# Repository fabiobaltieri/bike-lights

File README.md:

# Bike helmet head and tail light with remote control

This project is a head light and tail light electronic and CAD design,
featuring a handlebar mounted remote control for on/off operation, high beam
and rear stop light.

Contents
----------------

  - `cad`: FreeCAD source files for the various mechanical parts
  - `firmware-remote`: firmware for the remote control
  - `headlight`: hardware files for the head light LED carrier (Eagle)
  - `red-cluster`: hardware files for the rear light LED carrier (Eagle)
  - `remote`: hardware files for the remote controller (Eagle)

  TODO: add tail light pcb and firmware files.

Tail Light
----------

The tail light module contains the electronics and rechargeable battery.

Features:

  - Power drivers for front beam and rear lights (multiple channels).
  - Integrates a lithium battery charger via micro-USB (`MCP73831`).
  - Battery current and voltage monitoring (`INA219`).
  - Main microcontroller (`ATmega88PA`)
  - Low power radio for remote controlled operation (`nRF24L01+`).
  - Rear light uses an array of 4x3 red LEDs.

The module has a custom 3D printed case, and integrates a magnet to mount on
the rear helmet light slot found on many Giant helmets (meant to be used with
`Numen Link` lights). The magnet is glued to the case with epoxy.

Since the rear light module is removable, it includes two spring loaded
contacts (P/N: `Harwin P70-1020045R`) to drive the front headlight, which is
fixed on the helmet and wired to two matching copper tape pads on the rear
light slot.

  NOTE: the tail light module controller board currently in the repository has
  been designed for a different application, which is why the LEDs are driven
  using a set of motor drivers (`DRV8830`) rather than LED drivers. The design is
  unnecessarily complicated and has some unused components. I may eventually
  redesign a dedicated board from scratch.

Head Light
----------

The head light is mounted on the front side of the helmet, and it's made of a
cylindrical carrier with a flat side to match the helmet curvature, a front
lens (biconvex lens reused from a first gen Cardboard), a conical spacer
covered in foil to act as a reflector and a LED carrier board with a 5x5mm CREE
high power LED (P/N: `XMLBWT`) and a lock ring to secure the whole assembly.

All support components are 3D printed, and the internal components are 25mm
diameter (driven by the lens).  The whole assembly is mounted on the helmet
using `3M VHB` adhesive foam type (I've used the 1.1 thick 4941P type, general
purpose).

The LED carrier board has power contacts and LED on the top layer (front) and a
filled plane on the bottom layer (rear), which is electrically neutral and
connected to the thermal pad of the LED.  This should give a minimum level of
water proofing and heat sinking.

The wiring to the tail light module is done with magnet wire through the foam
body of the helmet, and mostly hidden behind the internal padding.

Handlebar Remote
----------------

The remote uses a small custom board, meant to be mounted on the bike brake
lever assembly.

Features:

  - Operates from a single CR2032 non-rechargeable Lithium battery.
  - Main microcontroller (`ATmega88PA`), stays most of its life in power down
    state waiting for a button press, extremely low power consumption.
  - Three tactile buttons for on/off, position light and high beam.
  - One SMD low profile reed switch (`Coto CT05-1535-J1`) for brake operation
    detection.

The reed switch is activated through a small magnet mounted on the actual brake
lever using a 3D printed carrier and secured with VHB tape.

The remote control board is enclosed in a 3D printed case, with a set of
matching flexible domes to allow clicking on the contacts through the plastic,
covered with generic double sided tape to (hopefully) make it waterproof.

The remote mounts on the brake assembly on a support bracket fixed on the
brake itself, and locks in place with a set of matching magnets.

TODO: actually build this.

Demo
----

[Short video of the whole system operation](https://youtu.be/Jjlq_EyCdOQ).

I want one!
-----------

Good! This whole design though is custom fit to the helmet and bike that I own,
so you'll have to fork your own version, adapt and build the various parts.

If you are just looking for an off the shelf product with similar features,
there are many options available, including:

  - Garmin Varia
  - Trek Bontrager RT series
  - Gemini lights
  - CatEye Rapid X2 Kinetic

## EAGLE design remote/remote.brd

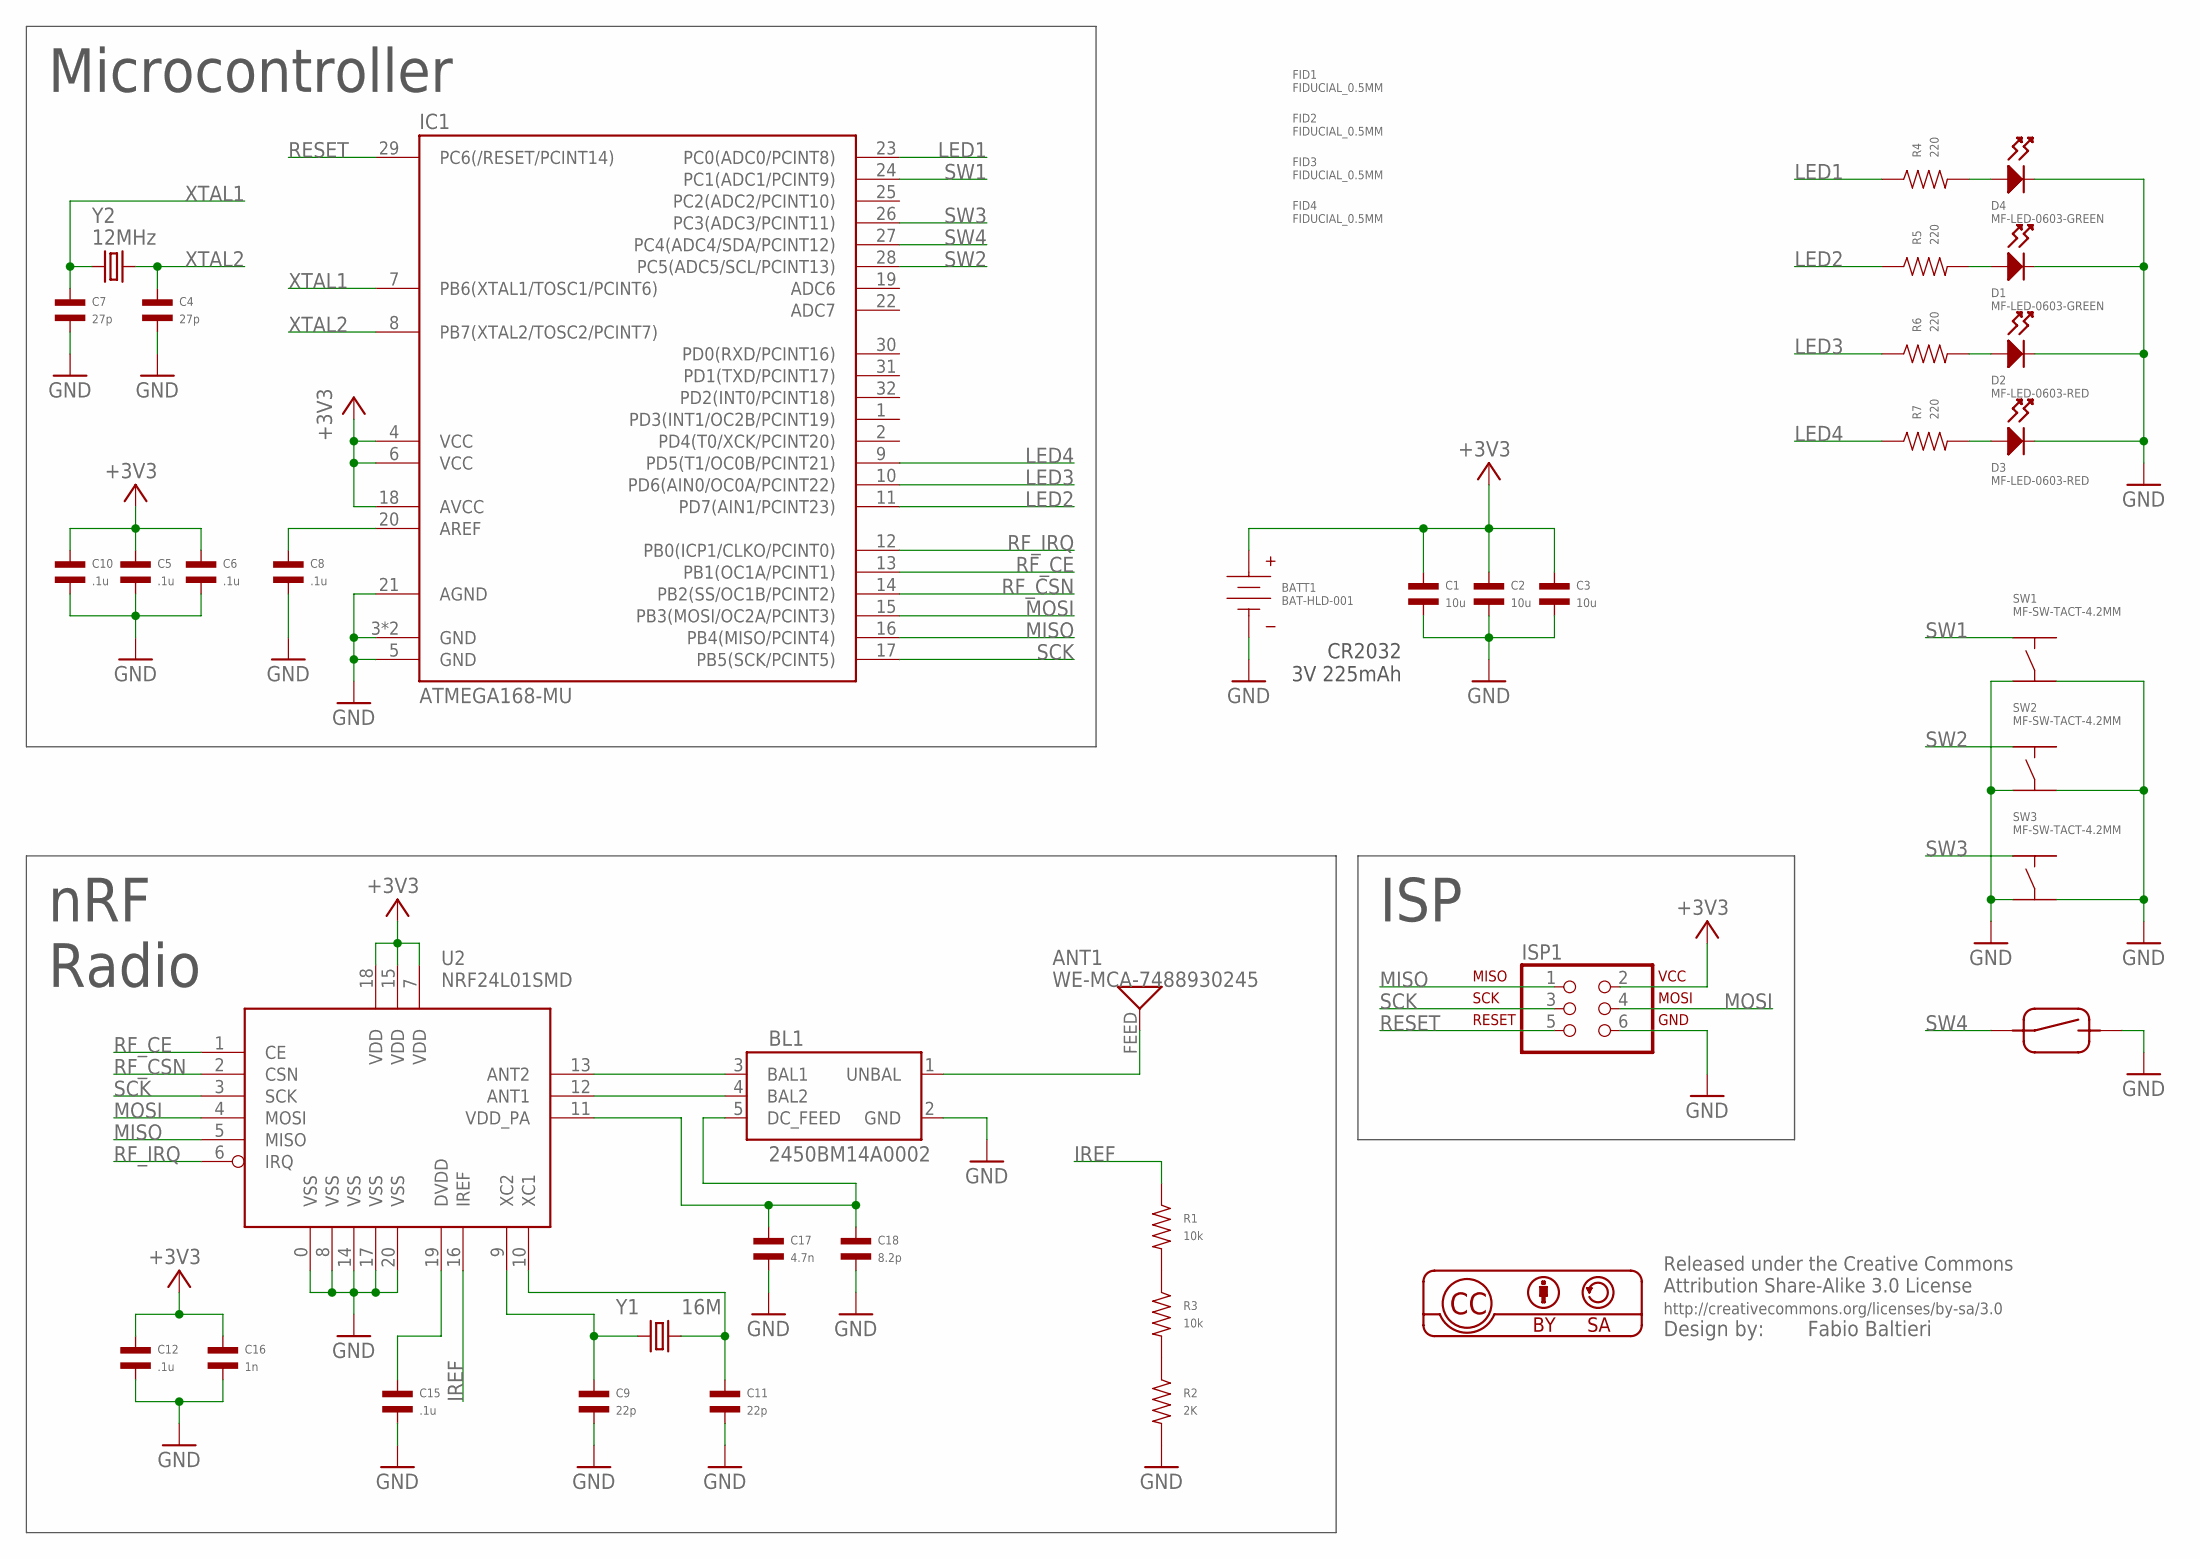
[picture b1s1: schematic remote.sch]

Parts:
ANT1: WE-MCA-7488930245; WE-MCA
BATT1: BAT-HLD-001
BL1: 2450BM14A0002; 0603_BALUN
C1, C2, C3: 10u; C1206; MPN MF-CAP-1206-10uF
C4, C7: 27p; C0402; MPN MF-CAP-0402-27p
C5, C6, C8, C10, C12, C15: .1u; C0402; MPN MF-CAP-0402-0.1uF
C9, C11: 22p; C0402; MPN MF-CAP-0402-22p
C16: 1n; C0402; MPN MF-CAP-0402-1nF
C17: 4.7n; C0402; MPN MF-CAP-0402-4.7nF
C18: 8.2p; C0402; MPN MF-CAP-0402-8.2pF
D1, D4: MF-LED-0603-GREEN; LED0603
D2, D3: MF-LED-0603-RED; LED0603
FID1, FID2, FID3, FID4: FIDUCIAL_0.5MM
IC1: ATMEGA168-MU; MLF32-TH
ISP1: ISP-AVR910PTH; 2X03
R1, R3: 10k; R0402; MPN MF-RES-0402-10K
R2: 2K; R0402; MPN MF-RES-0402-2K
R4, R5, R6, R7: 220; R0402; MPN MF-RES-0402-220
SW1, SW2, SW3: MF-SW-TACT-4.2MM; TACT4.2MM
SW4: CT05-XXXX-J1
U2: NRF24L01SMD; QFN20
Y1: 16M; CRYSTAL-SMD-5X3
Y2: 12MHz; CRYSTAL-SMD-5X3

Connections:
+3V3: BATT1.POS_0 (POS), BATT1.POS_1 (POS), C1.P$1, C2.P$1, C3.P$1, C5.P$1, C6.P$1, C10.P$1, C12.P$1, C16.P$1, IC1.4 (VCC), IC1.6 (VCC), IC1.18 (AVCC), ISP1.2, U2.7 (VDD), U2.15 (VDD), U2.18 (VDD)
GND: BATT1.NEG_0 (NEG), BL1.2 (GND), C1.P$2, C2.P$2, C3.P$2, C4.P$2, C5.P$2, C6.P$2, C7.P$2, C8.P$2, C9.P$2, C10.P$2, C11.P$2, C12.P$2, C15.P$2, C16.P$2, C17.P$2, C18.P$2, D1.CATHODE, D2.CATHODE, D3.CATHODE, D4.CATHODE, IC1.3 (GND), IC1.5 (GND), IC1.21 (AGND), IC1.TH (GND), ISP1.6, R2.P$2, SW1.P$3, SW1.P$4, SW2.P$3, SW2.P$4, SW3.P$3, SW3.P$4, SW4.P$2 (B), U2.0 (VSS), U2.8 (VSS), U2.14 (VSS), U2.17 (VSS), U2.20 (VSS)
IREF: R1.P$1, U2.16 (IREF)
LED1: IC1.23 (PC0(ADC0/PCINT8)), R4.P$1
LED2: IC1.11 (PD7(AIN1/PCINT23)), R5.P$1
LED3: IC1.10 (PD6(AIN0/OC0A/PCINT22)), R6.P$1
LED4: IC1.9 (PD5(T1/OC0B/PCINT21)), R7.P$1
MISO: IC1.16 (PB4(MISO/PCINT4)), ISP1.1, U2.5 (MISO)
MOSI: IC1.15 (PB3(MOSI/OC2A/PCINT3)), ISP1.4, U2.4 (MOSI)
unnamed: R2.P$1, R3.P$2
unnamed: C8.P$1, IC1.20 (AREF)
unnamed: R1.P$2, R3.P$1
unnamed: D3.ANODE, R7.P$2
unnamed: BL1.4 (BAL2), U2.12 (ANT1)
unnamed: BL1.3 (BAL1), U2.13 (ANT2)
unnamed: D2.ANODE, R6.P$2
unnamed: D1.ANODE, R5.P$2
unnamed: D4.ANODE, R4.P$2
unnamed: BL1.5 (DC_FEED), C17.P$1, C18.P$1, U2.11 (VDD_PA)
unnamed: C15.P$1, U2.19 (DVDD)
unnamed: C11.P$1, U2.10 (XC1), Y1.3 (2)
unnamed: C9.P$1, U2.9 (XC2), Y1.1
unnamed: ANT1.FEED, BL1.1 (UNBAL)
RESET: IC1.29 (PC6(/RESET/PCINT14)), ISP1.5
RF_CE: IC1.13 (PB1(OC1A/PCINT1)), U2.1 (CE)
RF_CSN: IC1.14 (PB2(SS/OC1B/PCINT2)), U2.2 (CSN)
RF_IRQ: IC1.12 (PB0(ICP1/CLKO/PCINT0)), U2.6 (IRQ)
SCK: IC1.17 (PB5(SCK/PCINT5)), ISP1.3, U2.3 (SCK)
SW1: IC1.24 (PC1(ADC1/PCINT9)), SW1.P$1
SW2: IC1.28 (PC5(ADC5/SCL/PCINT13)), SW2.P$1
SW3: IC1.26 (PC3(ADC3/PCINT11)), SW3.P$1
SW4: IC1.27 (PC4(ADC4/SDA/PCINT12)), SW4.P$1 (A)
XTAL1: C7.P$1, IC1.7 (PB6(XTAL1/TOSC1/PCINT6)), Y2.1
XTAL2: C4.P$1, IC1.8 (PB7(XTAL2/TOSC2/PCINT7)), Y2.3 (2)

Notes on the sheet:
CR2032 3V 225mAh
Microcontroller
ISP
nRF
Radio

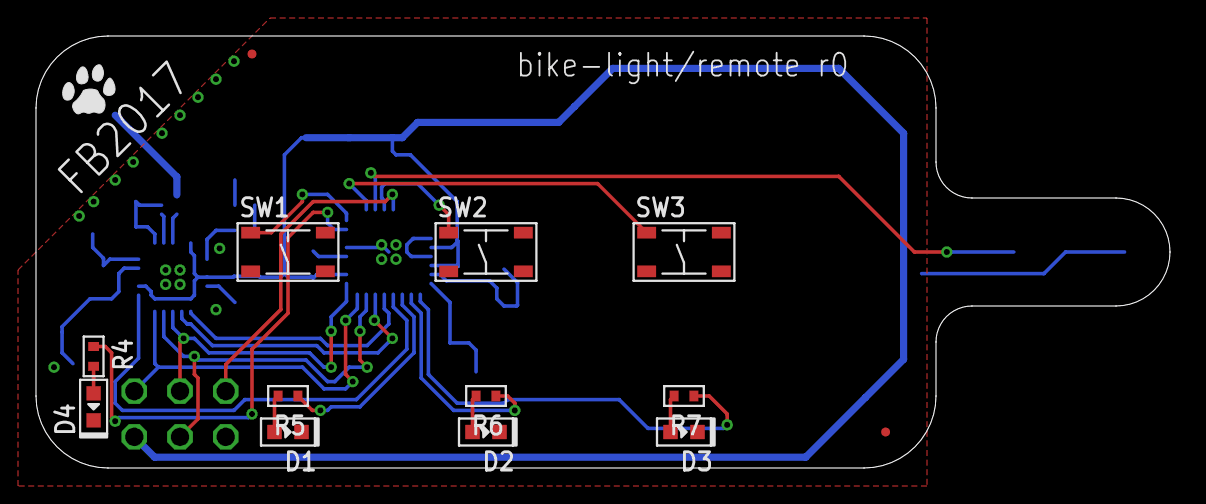
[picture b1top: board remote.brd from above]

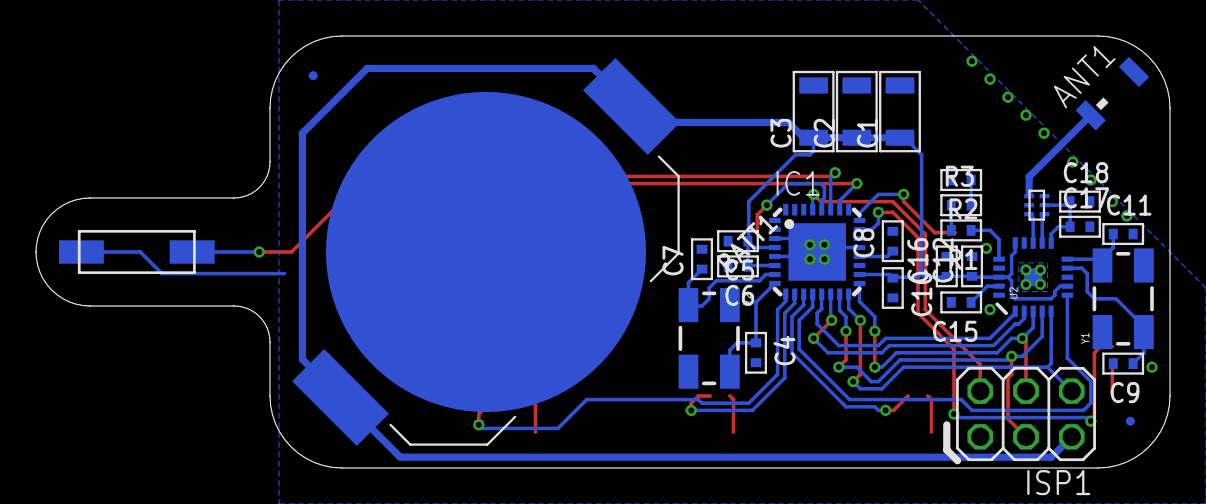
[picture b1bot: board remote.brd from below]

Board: 2 copper layers, 63.0 x 24.0 mm, 44 parts (30 on the bottom side), 34 nets.

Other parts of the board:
U$1: CAT-L

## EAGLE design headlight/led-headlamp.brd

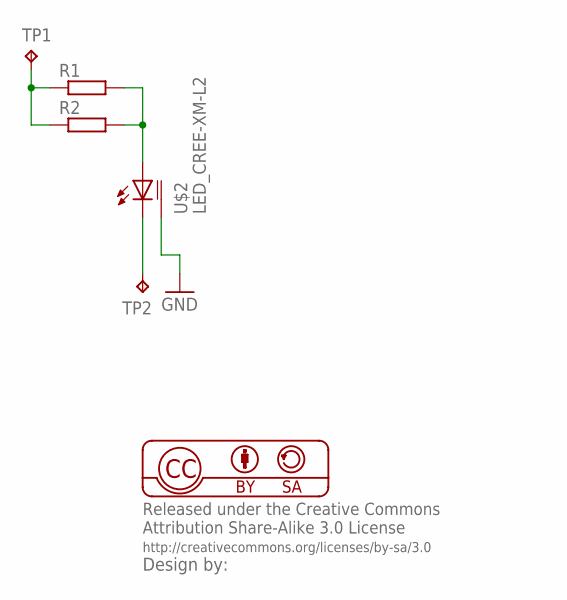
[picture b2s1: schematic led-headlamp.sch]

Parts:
R1, R2: R-EU_R0805; R0805
TP1, TP2: TPTP18R; TP18R
U$2: LED_CREE-XM-L2; XLAMP_5X5

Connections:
GND: U$2.TH
unnamed: TP2.TP, U$2.K (C)
unnamed: R1.1, R2.1, TP1.TP
unnamed: R1.2, R2.2, U$2.A

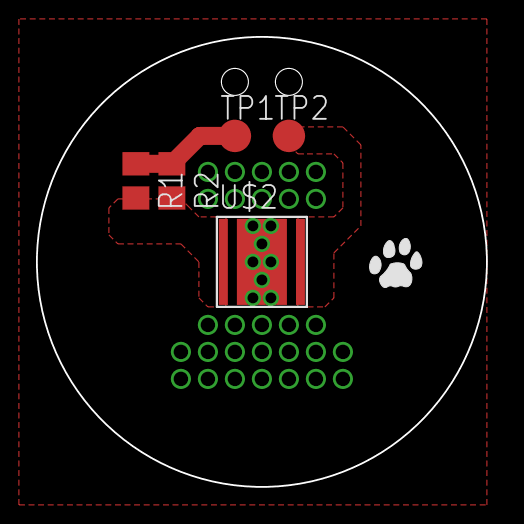
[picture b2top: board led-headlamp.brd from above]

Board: 2 copper layers, 25.0 x 25.0 mm, 6 parts (0 on the bottom side), 3 nets.

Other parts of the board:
U$1: CAT-L

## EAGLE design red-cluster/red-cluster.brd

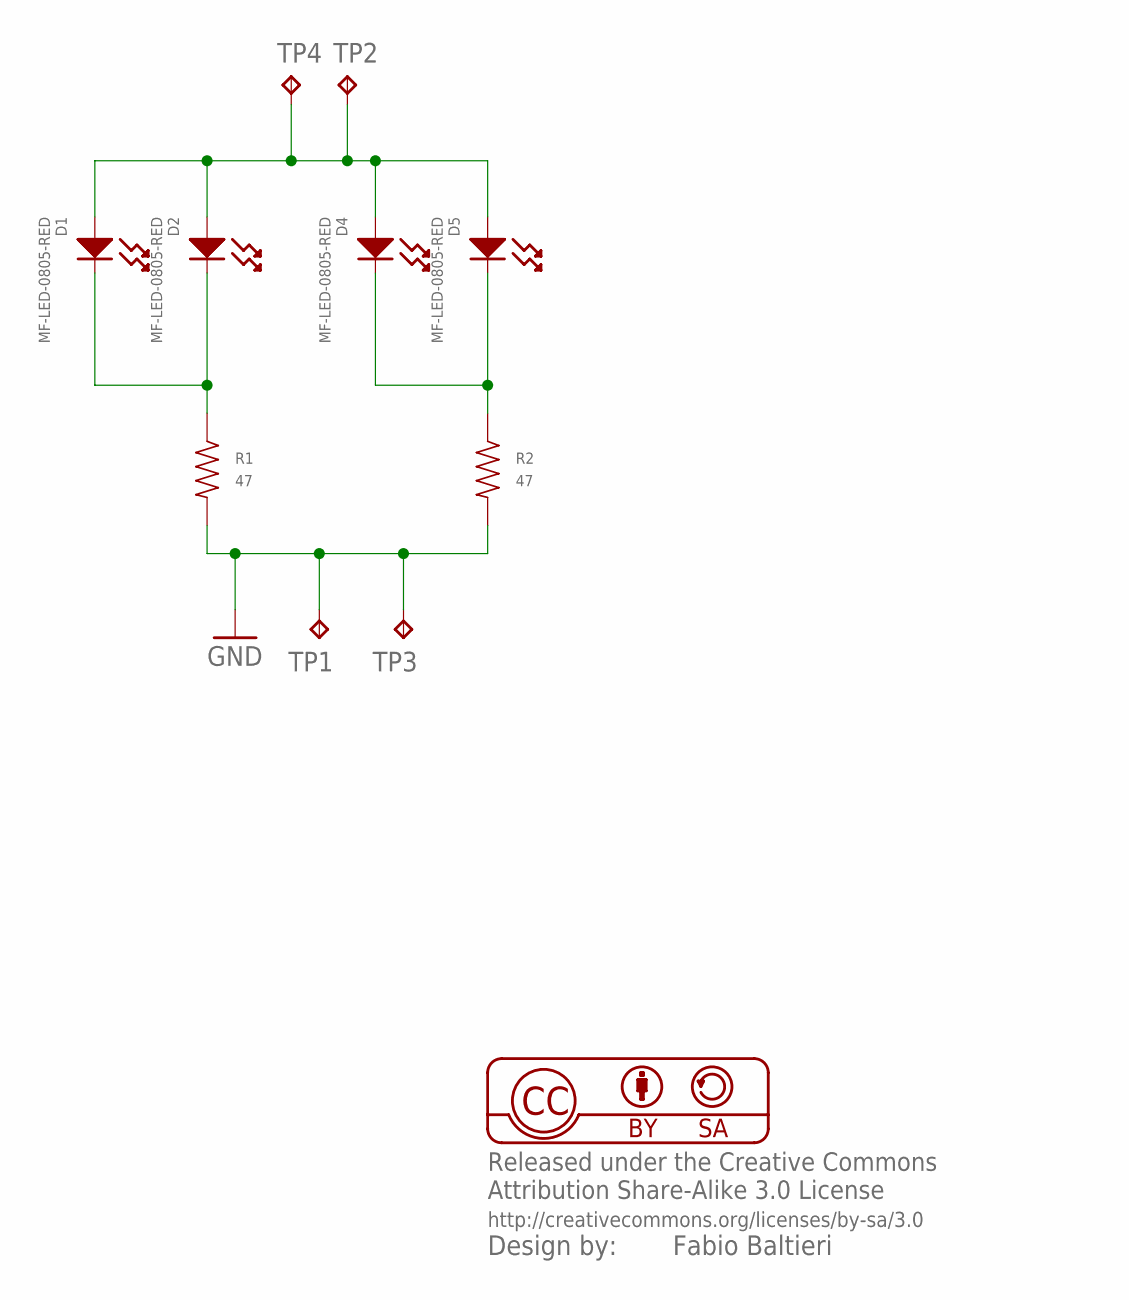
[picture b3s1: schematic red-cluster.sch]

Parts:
D1, D2, D4, D5: MF-LED-0805-RED; LED0805
R1, R2: 47; R0805
TP1, TP2, TP3, TP4: TPTP15R; TP15R

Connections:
GND: R1.P$2, R2.P$2, TP1.TP, TP3.TP
unnamed: D1.CATHODE, D2.CATHODE, R1.P$1
unnamed: D4.CATHODE, D5.CATHODE, R2.P$1
unnamed: D1.ANODE, D2.ANODE, D4.ANODE, D5.ANODE, TP2.TP, TP4.TP

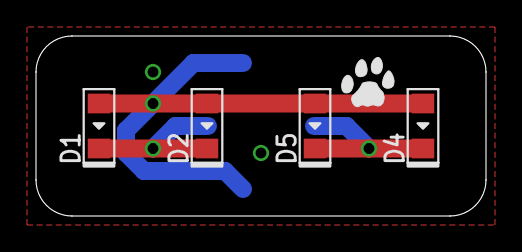
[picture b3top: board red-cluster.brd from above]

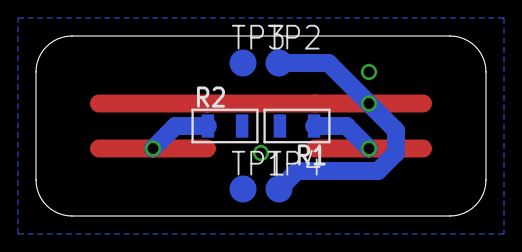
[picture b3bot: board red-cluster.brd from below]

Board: 2 copper layers, 25.0 x 10.0 mm, 11 parts (6 on the bottom side), 4 nets.

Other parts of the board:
U$1: CAT-L

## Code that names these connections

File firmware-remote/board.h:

/* LED */
#define LED1_PORT	PORTC
#define LED1_DDR	DDRC
#define LED1		PC0

#define LED234_PORT	PORTD
#define LED234_DDR	DDRD
#define LED2		PD7
#define LED3		PD6
#define LED4		PD5

#define led1_on()	LED1_PORT |=  _BV(LED1)
#define led1_off()	LED1_PORT &= ~_BV(LED1)
#define led2_on()	LED234_PORT |=  _BV(LED2)
#define led2_off()	LED234_PORT &= ~_BV(LED2)
#define led3_on()	LED234_PORT |=  _BV(LED3)
#define led3_off()	LED234_PORT &= ~_BV(LED3)
#define led4_on()	LED234_PORT |=  _BV(LED4)
#define led4_off()	LED234_PORT &= ~_BV(LED4)

#define led_init() \
	do { \
		LED1_DDR |= _BV(LED1); \
		LED234_DDR |= _BV(LED2) | _BV(LED3) | _BV(LED4); \
	} while (0);

/* SPI */
#define SPI_DDR  DDRB
#define SPI_PORT PORTB
#define SPI_SS   PB2
#define SPI_SCK  PB5
#define SPI_MOSI PB3
#define SPI_MISO PB4

/* nRF24L01+ SPI */
#define NRF_DDR  DDRB
#define NRF_PORT PORTB
#define NRF_CS   SPI_SS
#define NRF_CE   PB1

#define nrf_cs_h() (NRF_PORT |=  _BV(NRF_CS))
#define nrf_cs_l() (NRF_PORT &= ~_BV(NRF_CS))
#define nrf_ce_h() (NRF_PORT |=  _BV(NRF_CE))
#define nrf_ce_l() (NRF_PORT &= ~_BV(NRF_CE))

#define NRF_PCMSK PCMSK0
#define NRF_PCINT _BV(PCINT0)

/* Switches */
#define SW_PORT        PORTC
#define SW_PIN         PINC
#define SW1            PC1
#define SW2            PC5
#define SW3            PC3
#define SW4            PC4

#define sw_init() \
	do { \
		SW_PORT |= _BV(SW1) | _BV(SW2) | _BV(SW3) | _BV(SW4); \
	} while (0)

#define sw1_read()	(!(SW_PIN & _BV(SW1)))
#define sw2_read()	(!(SW_PIN & _BV(SW2)))
#define sw3_read()	(!(SW_PIN & _BV(SW3)))
#define sw4_read()	(!(SW_PIN & _BV(SW4)))

#define SW_PCMSK PCMSK1
#define SW_PCINT (_BV(PCINT9) | _BV(PCINT11) | _BV(PCINT12) | _BV(PCINT13))

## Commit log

2017-06-04 red-cluster: initial commit
2017-06-11 Add headlamp hw files
2017-06-11 cad: add mount and light CAD files
2017-08-12 cad: random updates
2017-08-14 hw: remote: rev0, as sent to the fab
2017-09-10 firmware-remote: initial import, board setup
2017-09-10 remote: drop unsused net
2017-09-10 remote-fw: add nrf and spi drivers
2017-09-10 remote-sw: setup pcint on switches
2017-09-15 add a .gitignore file
2017-10-02 remote: schematics clean up
2017-10-02 cad: helmet block, clean up cad files
2017-10-09 cad: add cad file for box and magnet holder
2017-10-09 gitignore: add a bunch of prod file extensions
2017-10-09 fw: add basic button handling
2017-10-09 fw: change wdt to .25s, only poll and debounce when needed
2017-10-09 fw: add tx delay, handle missing brake magnet
2017-10-13 add README.md
2017-10-25 cad: add mounting bracket and base

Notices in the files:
parts and their libraries:
balto: Released under the Creative Commons
balto: http://creativecommons.org/licenses/by-sa/3.0
SparkFun: Licensing: CC v3.0 Share-Alike You are welcome to use this library for commercial purposes.
